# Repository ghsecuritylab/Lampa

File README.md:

# Lampa 

1. ESP 
nazwa: ESO_0
haslo: configesp
config ip:  192.168.4.1/setup

Kod piszemy pod easyesp Arduino
https://www.letscontrolit.com/wiki/index.php/Tutorial_Arduino_Firmware_Upload

wszystkie dotychczasowe zmiany dotycza pliku _P099_MCP41XXX.ino

2. Domoticz
trzeba recznie wpisac adres IP EasyESP
domoticz/scripts/dzVents/scripts/skrypt.lua

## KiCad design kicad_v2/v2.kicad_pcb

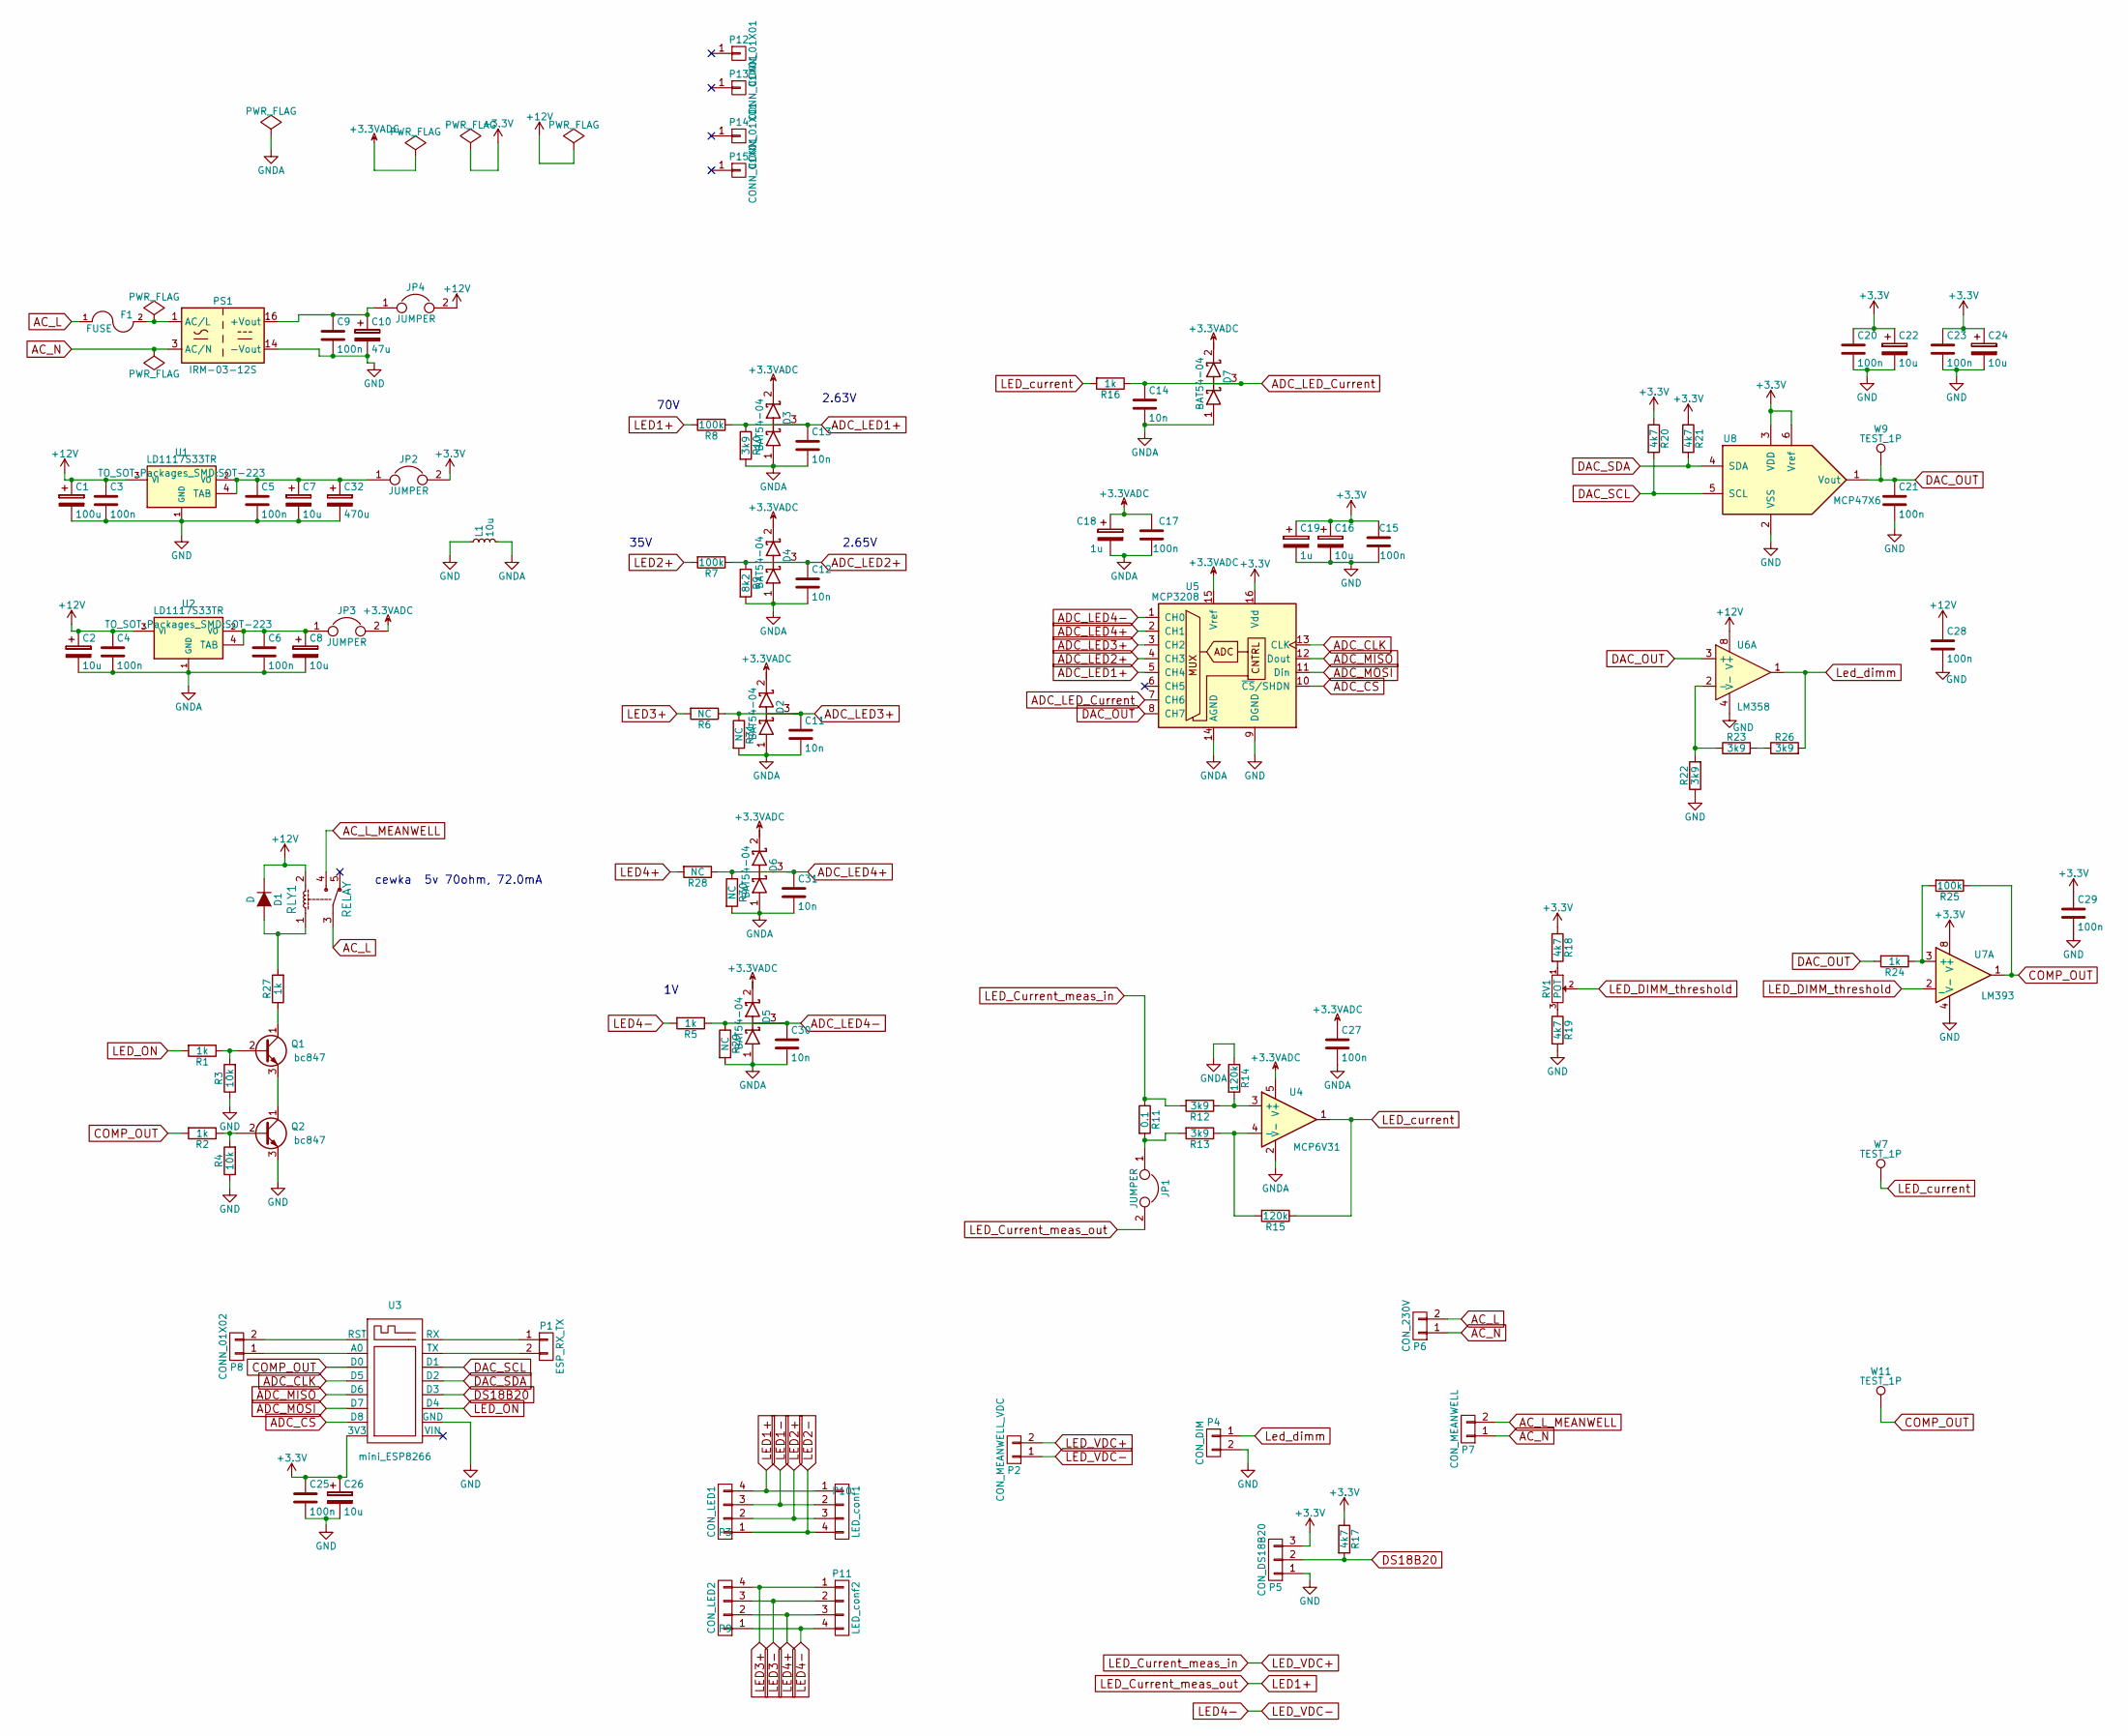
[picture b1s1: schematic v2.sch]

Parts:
C1: 100u; c_elec_6.3x5.3
C2, C7, C8, C16, C22, C24, C26: 10u; TantalC_SizeB_EIA-3528_Reflow
C3, C4, C5, C6, C9, C15, C17, C20, C21, C23, C25, C27, C28, C29: 100n; C_0805
C10: 47u; c_elec_5x5.3
C11, C12, C13, C14, C30, C31: 10n; C_0805
C18, C19: 1u; TantalC_SizeA_EIA-3216_Reflow
C32: 470u; C_Radial_D10_L21_P5
D1: D; SOD-80
D2, D3, D4, D5, D6, D7: BAT54-04; SOT-23
F1: FUSE; Fuseholder5x20_horiz_open_inline_Type-I
JP1, JP2, JP3, JP4: JUMPER; Pin_Header_Straight_1x02
L1: 10u; Choke_Horizontal_RM10mm
P1: ESP_RX_TX; Pin_Header_Straight_1x02
P2: CON_MEANWELL_VDC; bornier2
P3: CON_LED1; bornier4
P4: CON_DIM; bornier2
P5: CON_DS18B20; bornier3
P6: CON_230V; bornier2
P7: CON_MEANWELL; bornier2
P8: CONN_01X02; Pin_Header_Straight_1x02
P9: CON_LED2; bornier4
P10: LED_conf1; Pin_Header_Straight_1x04
P11: LED_conf2; Pin_Header_Straight_1x04
P12, P13, P14, P15: CONN_01X01; 1pin
PS1: IRM-03-12S; Converter_ACDC_MeanWell_IRM-03-xx_THT
Q1, Q2: bc847; SOT-23
R1, R2, R5, R16, R24, R27: 1k; R_0805
R3, R4: 10k; R_0805
R6, R28, R29, R30, R31: NC; R_0805
R7, R8, R25: 100k; R_0805
R9: 8k2; R_0805
R10, R12, R13, R22, R23, R26: 3k9; R_0805
R11: 0.1; R_1206
R14, R15: 120k; R_0805
R17, R18, R19, R20, R21: 4k7; R_0805
RLY1: RELAY; Relay_SANYOU_SRD_Series_Form_C
RV1: POT; Potentiometer_Triwood_RM-065
U1, U2: LD1117S33TR; SOT-223
U3: mini_ESP8266; Mini_ESP8266
U4: MCP6V31; SC-70-5
U5: MCP3208; SO-16-N
U6: LM358; SOIC-8_3.9x4.9mm_Pitch1.27mm
U7: LM393; SOIC-8_3.9x4.9mm_Pitch1.27mm
U8: MCP47X6; SOT-23-6
W7, W9, W11: TEST_1P; 1Pin

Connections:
+3.3VADC: C17.2, C18.1, C27.1, D2.2 (K), D3.2 (K), D4.2 (K), D5.2 (K), D6.2 (K), D7.2 (K), JP3.2, U4.5 (V+), U5.15 (Vref)
+3V3: C15.2, C16.1, C19.1, C20.1, C22.1, C23.1, C24.1, C25.1, C26.1, C29.1, JP2.2, P5.3, R17.1, R18.1, R20.1, R21.1, U3.8 (3V3), U5.16 (Vdd), U7.8 (V+), U8.3 (VDD), U8.6 (Vref)
+12V: C1.1, C2.1, C3.1, C4.1, C28.1, D1.K, JP4.2, RLY1.2, U1.3 (VI), U2.3 (VI), U6.8 (V+)
AC_L: F1.1, P6.2, RLY1.3
AC_L_MEANWELL: P7.2, RLY1.4
AC_N: P6.1, P7.1, PS1.3 (AC/N)
ADC_CLK: U3.4 (D5), U5.13 (CLK)
ADC_CS: U3.7 (D8), U5.10 (~CS~/SHDN)
ADC_LED1+: C13.1, D3.3 (common), R8.1, R10.1, U5.5 (CH4)
ADC_LED2+: C12.1, D4.3 (common), R7.1, R9.1, U5.4 (CH3)
ADC_LED3+: C11.1, D2.3 (common), R6.1, R31.1, U5.3 (CH2)
ADC_LED4+: C31.1, D6.3 (common), R28.1, R30.1, U5.2 (CH1)
ADC_LED4-: C30.1, D5.3 (common), R5.1, R29.1, U5.1 (CH0)
ADC_LED_Current: C14.1, D7.3 (common), R16.1, U5.7 (CH6)
ADC_MISO: U3.5 (D6), U5.12 (Dout)
ADC_MOSI: U3.6 (D7), U5.11 (Din)
COMP_OUT: R2.2, R25.1, U3.3 (D0), U7.1, W11.1
DAC_OUT: C21.1, R24.2, U5.8 (CH7), U6.3 (+), U8.1 (Vout), W9.1
DAC_SCL: R20.2, U3.14 (D1), U8.5 (SCL)
DAC_SDA: R21.2, U3.13 (D2), U8.4 (SDA)
DS18B20: P5.2, R17.2, U3.12 (D3)
GND: C1.2, C3.2, C5.2, C7.2, C9.2, C10.2, C15.1, C16.2, C19.2, C20.2, C21.2, C22.2, C23.2, C24.2, C25.2, C26.2, C28.2, C29.2, C32.2, L1.1, P4.2, P5.1, PS1.14 (-Vout), Q2.3 (E), R3.1, R4.1, R19.2, R22.1, U1.1 (GND), U3.10 (GND), U5.9 (DGND), U6.4 (V-), U7.4 (V-), U8.2 (VSS)
GNDA: C2.2, C4.2, C6.2, C8.2, C11.2, C12.2, C13.2, C14.2, C17.1, C18.2, C27.2, C30.2, C31.2, D2.1 (A), D3.1 (A), D4.1 (A), D5.1 (A), D6.1 (A), D7.1 (A), L1.2, R9.2, R10.2, R14.1, R29.2, R30.2, R31.2, U2.1 (GND), U4.2 (V-), U5.14 (AGND)
LED1+: JP1.2, P3.4, P10.1, R8.2
LED1-: P3.3, P10.2
LED2+: P3.2, P10.3, R7.2
LED2-: P3.1, P10.4
LED3+: P9.4, P11.1, R6.2
LED3-: P9.3, P11.2
LED4+: P9.2, P11.3, R28.2
LED4-: P2.1, P9.1, P11.4, R5.2
LED_Current_meas_in: P2.2, R11.1, R12.2
LED_DIMM_threshold: RV1.2, U7.2 (_)
LED_ON: R1.2, U3.11 (D4)
LED_current: R15.1, R16.2, U4.1, W7.1
Led_dimm: P4.1, R26.2, U6.1
unnamed: C6.1, C8.1, JP3.1, U2.2 (VO), U2.4 (TAB)
unnamed: C9.1, C10.1, JP4.1, PS1.16 (+Vout)
unnamed: C5.1, C7.1, C32.1, JP2.1, U1.2 (VO), U1.4 (TAB)
unnamed: D1.A, R27.2, RLY1.1
unnamed: F1.2, PS1.1 (AC/L)
unnamed: JP1.1, R11.2, R13.2
unnamed: P1.1, U3.16 (RX)
unnamed: P1.2, U3.15 (TX)
unnamed: P8.1, U3.2 (A0)
unnamed: P8.2, U3.1 (RST)
unnamed: Q1.1 (C), R27.1
unnamed: Q1.2 (B), R1.1, R3.2
unnamed: Q1.3 (E), Q2.1 (C)
unnamed: Q2.2 (B), R2.1, R4.2
unnamed: R12.1, R14.2, U4.3 (+)
unnamed: R13.1, R15.2, U4.4 (-)
unnamed: R18.2, RV1.1
unnamed: R19.1, RV1.3
unnamed: R22.2, R23.1, U6.2 (-)
unnamed: R23.2, R26.1
unnamed: R24.1, R25.2, U7.3 (+)

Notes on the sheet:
70V
2.63V
35V
2.65V
cewka 5v 70ohm, 72.0mA

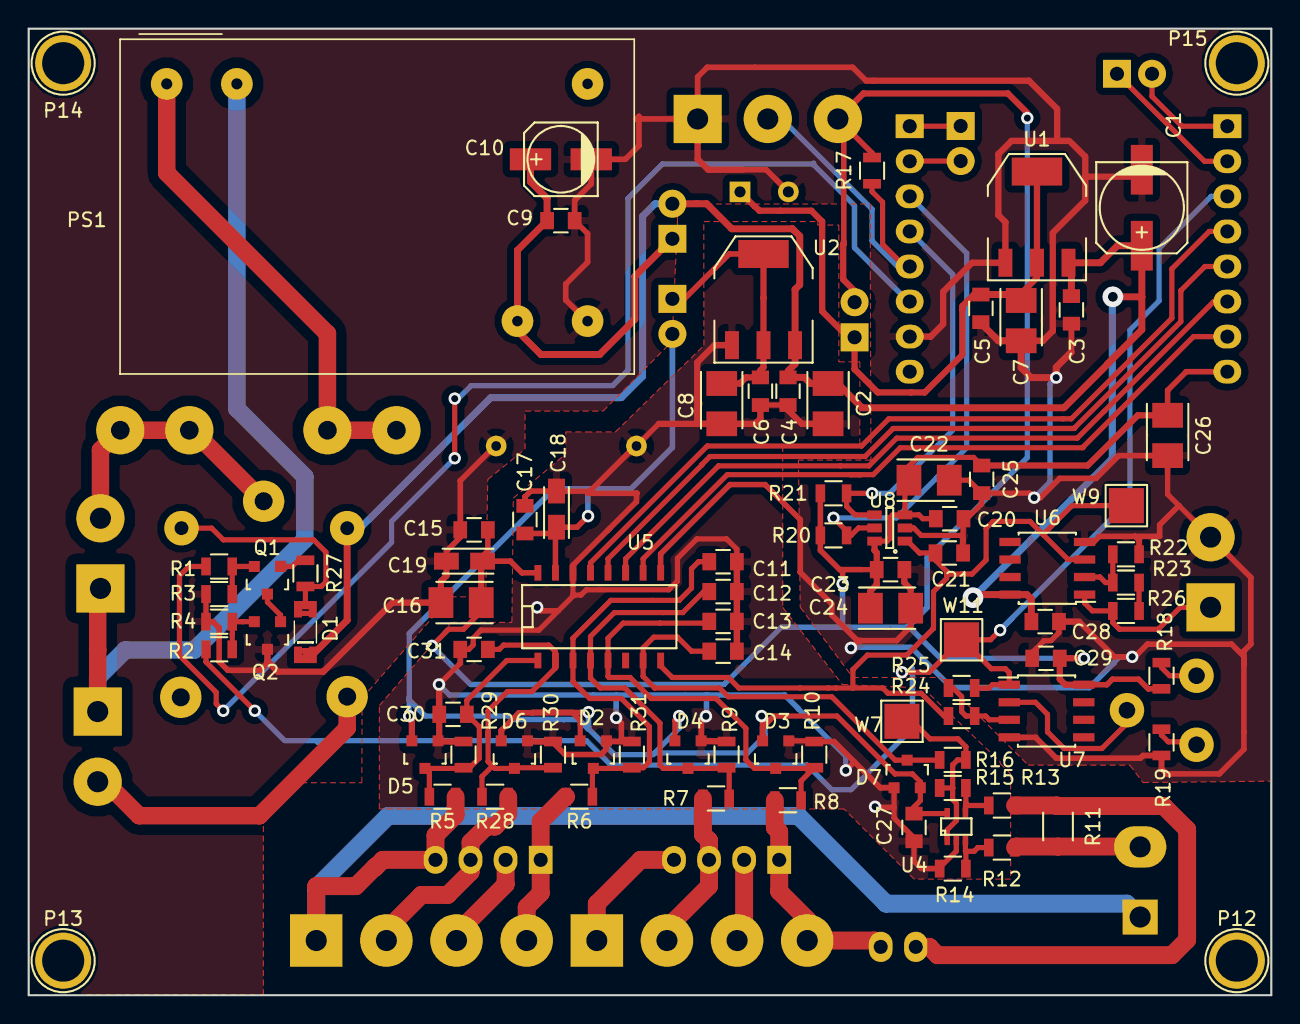
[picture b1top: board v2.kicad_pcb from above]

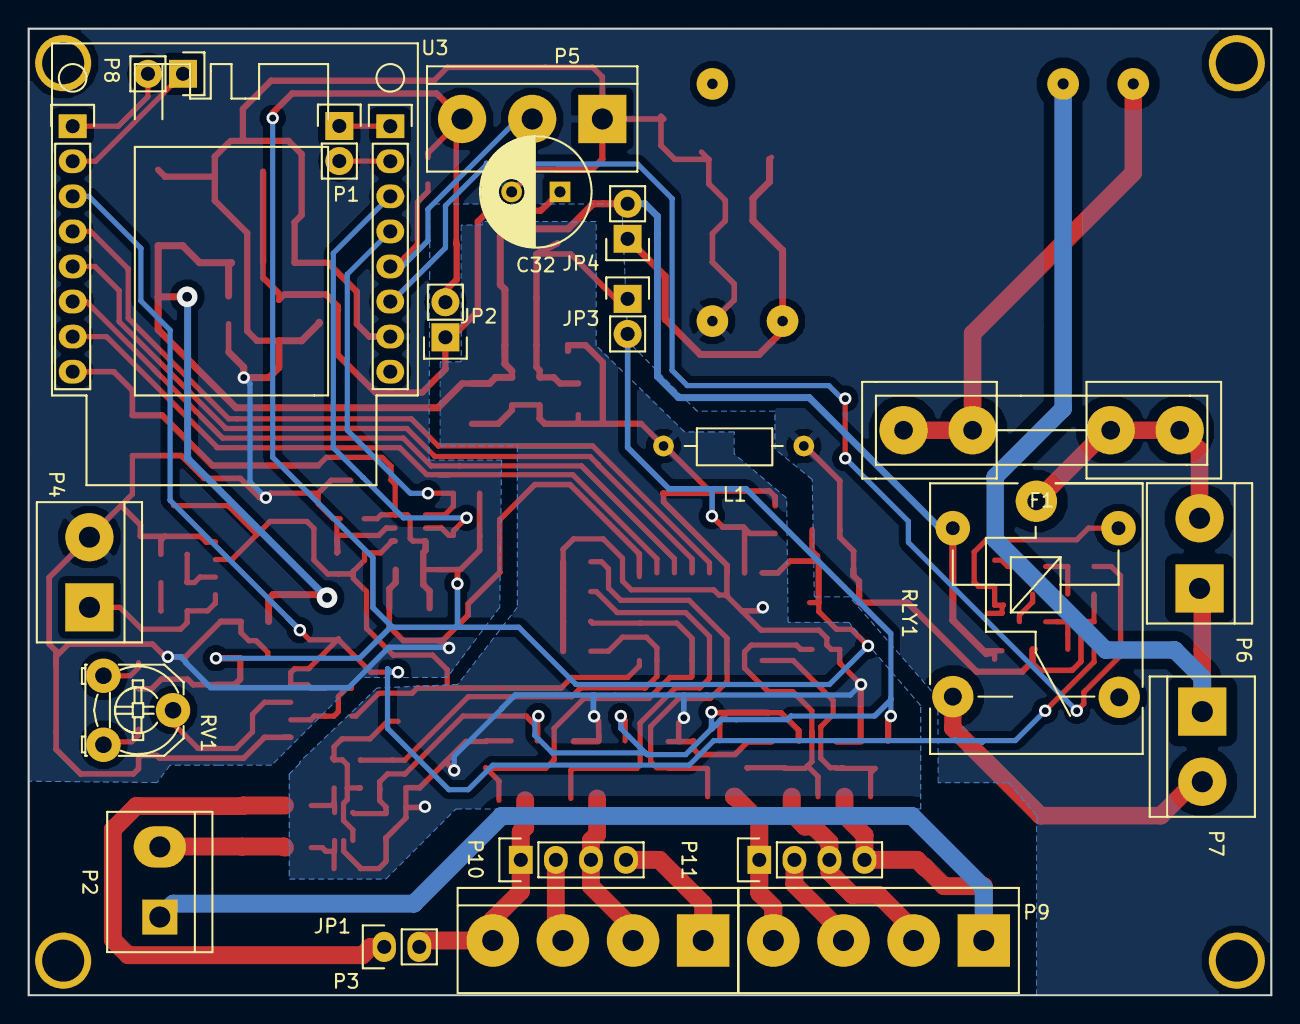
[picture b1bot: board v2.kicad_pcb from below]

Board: 2 copper layers, 90.0 x 70.0 mm, 107 parts (21 on the bottom side), 57 nets.

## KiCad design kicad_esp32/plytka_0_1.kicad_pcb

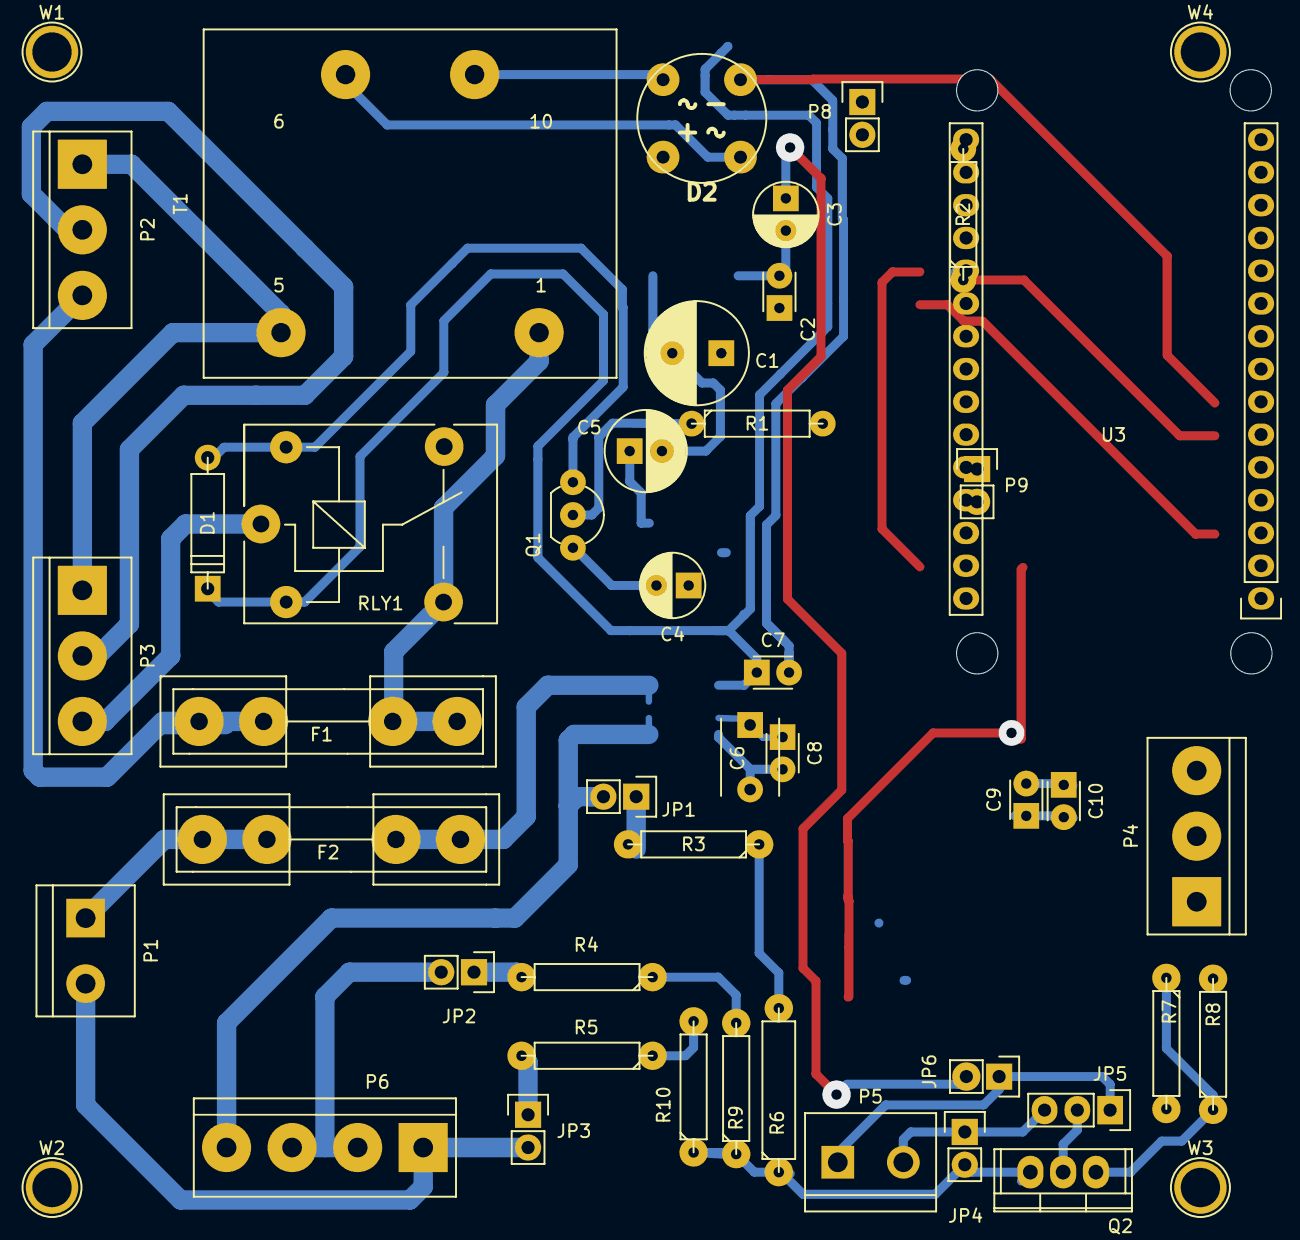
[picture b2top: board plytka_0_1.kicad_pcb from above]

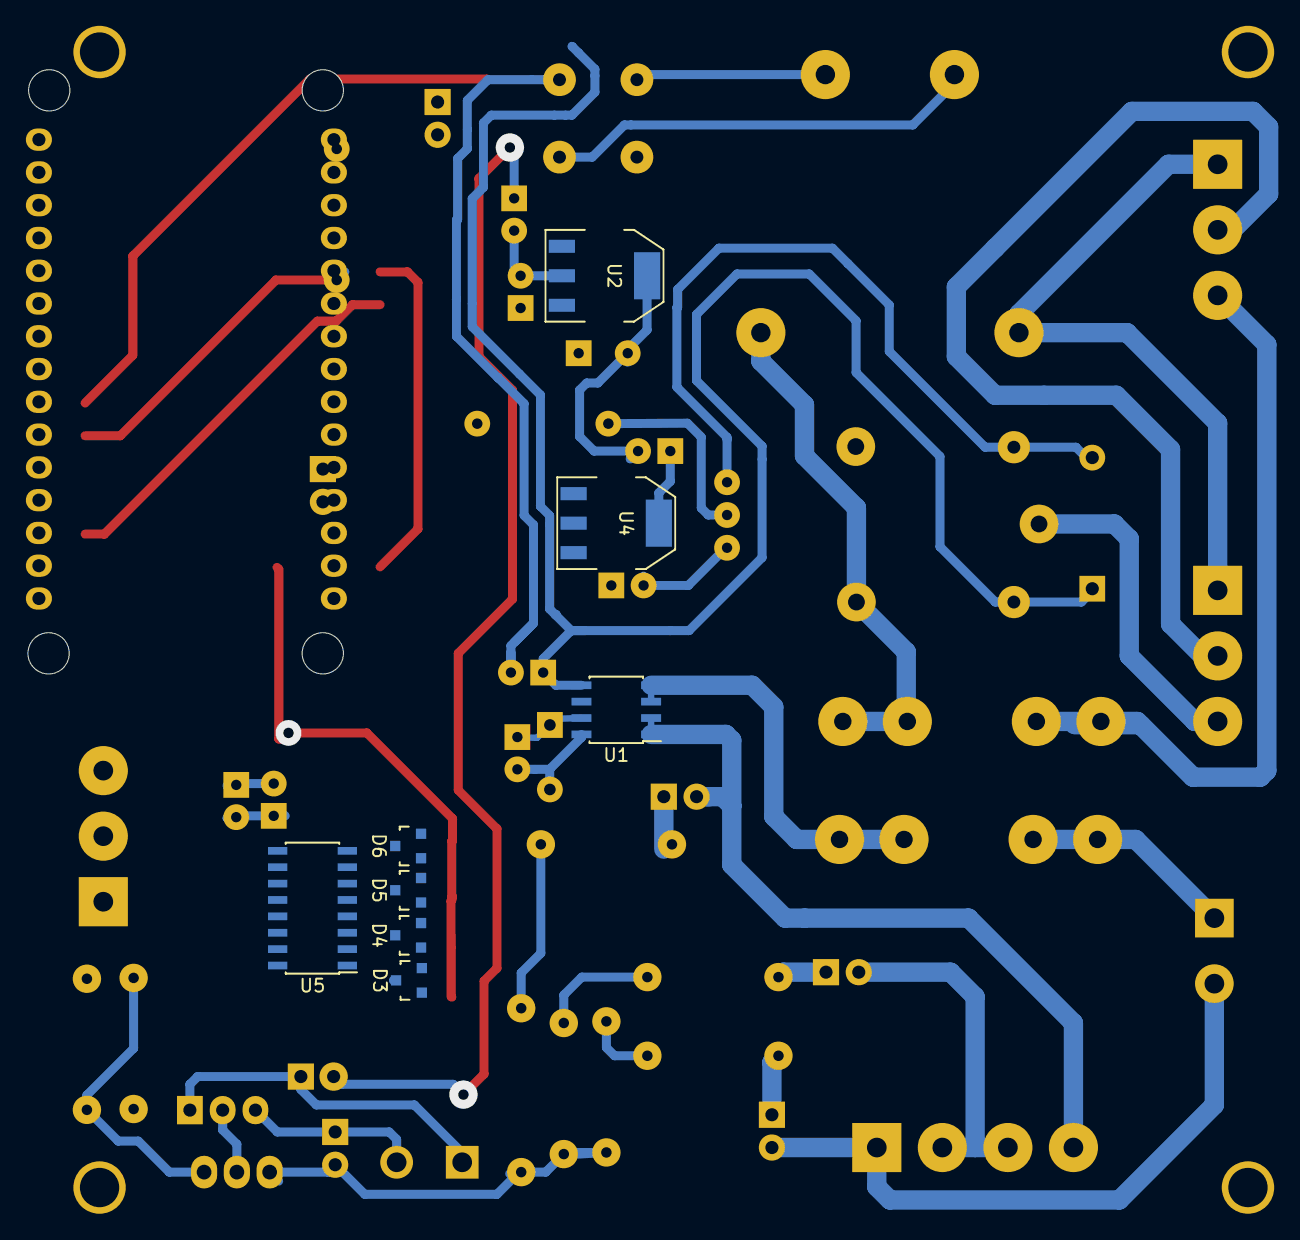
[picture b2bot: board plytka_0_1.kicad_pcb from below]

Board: 2 copper layers, 55 parts (8 on the bottom side), 42 nets.

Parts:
C1: 470u; C_Radial_D8_L13_P3.8
C2, C7, C9, C10: 100n; C_Disc_D3_P2.5
C3: 22u; C_Radial_D5_L6_P2.5
C4: 10u; C_Radial_D5_L11_P2.5
C5: 100u; C_Radial_D6.3_L11.2_P2.5
C6: 1n; C_Disc_D6_P5
C8: NC; C_Disc_D3_P2.5
D1: 1N4148; D4
D2: Diode_Bridge; bridge_wob
D3, D4, D5, D6: BAT54-04; SOT-23
F1, F2: FUSE; Fuseholder5x20_horiz_open_inline_Type-I
JP1, JP2, JP3: JUMPER(NC); Pin_Header_Straight_1x02
JP4, JP6: JUMPER; Pin_Header_Straight_1x02
JP5: JUMPER3; Pin_Header_Straight_1x03
P1: LED_SUPPY; bornier2
P2: 230V; bornier3
P3: MEAN_WELL; bornier3
P4: DS18b20_1; bornier3
P5: LED_DIMM; bornier2
P6: LEDs; bornier4
P8: ESP_PIN1(NC); Pin_Header_Straight_1x02
P9: ESP_PINS2(NC); Pin_Header_Straight_1x02
Q1: BC548; TO-92_Inline_Wide
Q2: IRL540N; TO-220
R1, R2: 4k7; R4
R3, R4: 100k; R4
R5, R10: (NC); R4
R6: 3k; R5
R7: 100; R4
R8: 10k; R4
R9: 5k; R4
RLY1: RELAY_T9AS5x1; Relay_SANYOU_SRD_Series_Form_C
T1: TRANSFO; Trafo_CHK-EI30-2VA_Neutral
U1: ACS712ELCTR-05B-T; SOIC-8_3.9x4.9mm_Pitch1.27mm
U2: TLE_4266; SOT-223
U3: NodeMCU_Amica_R2
U4: LD1117S50TR; SOT-223
U5: MCP3208; SOIC-16_3.9x9.9mm_Pitch1.27mm
W1, W2, W3, W4: HOLE; 1pin

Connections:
+3V3: C9.1, C10.2, D3.2, D4.2, D5.2, D6.2, P4.1, R2.1, U3.11, U3.16, U3.25, U5.15, U5.16
+5V: C5.1, C7.1, D1.1, RLY1.2, U1.8, U3.15, U4.2
+10V: C3.1, C4.1, JP6.2, U2.3, U4.3
ADC_LED1_IN+: D3.3, R3.1, R6.2, U5.8
ADC_LED2_IN-: D5.3, R5.1, R10.2, U5.4
ADC_LED_COMON: D4.3, R4.1, R9.2, U5.6
DIM+: JP5.1, JP6.1, P5.1
DIM-: JP4.1, JP5.3, P5.2
DS18b20: P4.2, R2.2, U3.27
ESP_PWM_OUT: R7.2, U3.28, U5.2
Earth_Protective: P2.2, P3.2
GND: C1.2, C2.2, C3.2, C4.2, C5.2, C6.2, C7.2, C8.2, C9.2, C10.1, D2.1, D3.1, D4.1, D5.1, D6.1, JP4.2, P4.3, Q1.3, Q2.3, R6.1, R8.2, R9.1, R10.1, U1.5, U2.2, U2.4, U3.10, U3.14, U3.17, U3.24, U4.1, U5.9, U5.14
LED1+: JP1.2, P6.4, U1.3, U1.4
LED1-: JP2.2, P6.2, P6.3
LED2-: JP3.2, P1.2, P6.1
LED_Current: D6.3, U1.7, U5.1
LED_ON: R1.2, U3.26
MCP_CLK: U3.23, U5.13
MCP_CS: U3.20, U5.10
MCP_DIN: U3.21, U5.11
MCP_DOUT: U3.22, U5.12
unnamed: C1.1, C2.1, D2.3, U2.1
unnamed: C6.1, C8.1, U1.6
unnamed: D1.2, Q1.1, RLY1.1
unnamed: D2.2, T1.7
unnamed: D2.4, T1.9
unnamed: F1.1, P2.3
unnamed: F1.2, RLY1.4, T1.1
unnamed: F2.2, U1.1, U1.2
unnamed: JP1.1, R3.2
unnamed: JP2.1, R4.2
unnamed: JP3.1, R5.2
unnamed: JP5.2, Q2.2
unnamed: P2.1, P3.1, T1.5
unnamed: P3.3, RLY1.3
unnamed: P8.1, U3.30
unnamed: P8.2, U3.29
unnamed: P9.1, U3.19
unnamed: P9.2, U3.18
unnamed: Q1.2, R1.1
unnamed: Q2.1, R7.1, R8.1
VAA: F2.1, P1.1

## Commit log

2018-10-23 added PWM and documentation
2018-11-12 added global config for IP and other scripts added KiCAD project
2018-11-13 power supply
2018-11-14 almost ready. time for choosing footprint. still no ADC
2018-11-15 ready for review
2018-11-17 schematic ready, board placed no routes
2018-11-18 almost final PCB
2018-11-19 pierwszy druk
2018-11-20 board_1_0
2019-01-22 swieci da sie sciemniac plytka nazywa sie new costam
2019-02-12 sadasdad
2019-02-18 21312
2019-03-01 new kicad + soft
2019-03-10 new version
2019-05-27 current version
2020-03-08 `vallen` is verified to be less than `len`, therefore, it can never be the case that `vallen >= len + sizeof(rhostname)`.
    This PR fixes the check so the `rhostname` array does not overflow.
    Reported-by: Github Security Lab <securitylab@github.com>
